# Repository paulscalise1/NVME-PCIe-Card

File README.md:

# NVME PCIe Card

A x4 PCIe to NVME adapter card for additional storage in PCIe Gen 4 and below compatable machines.
This board was created for the final project in ECEN 882 Passive Microwave Components at the University of Nebraska-Lincoln.

## PCB Design

## Validation

This board was tested with and on PCIe Gen 3 capable hardware. Read and write speeds top out near the real world limits of the hardware, thus proving at least PCIe Gen 3 performance metrics.

## TODO
Need to add full BOM.

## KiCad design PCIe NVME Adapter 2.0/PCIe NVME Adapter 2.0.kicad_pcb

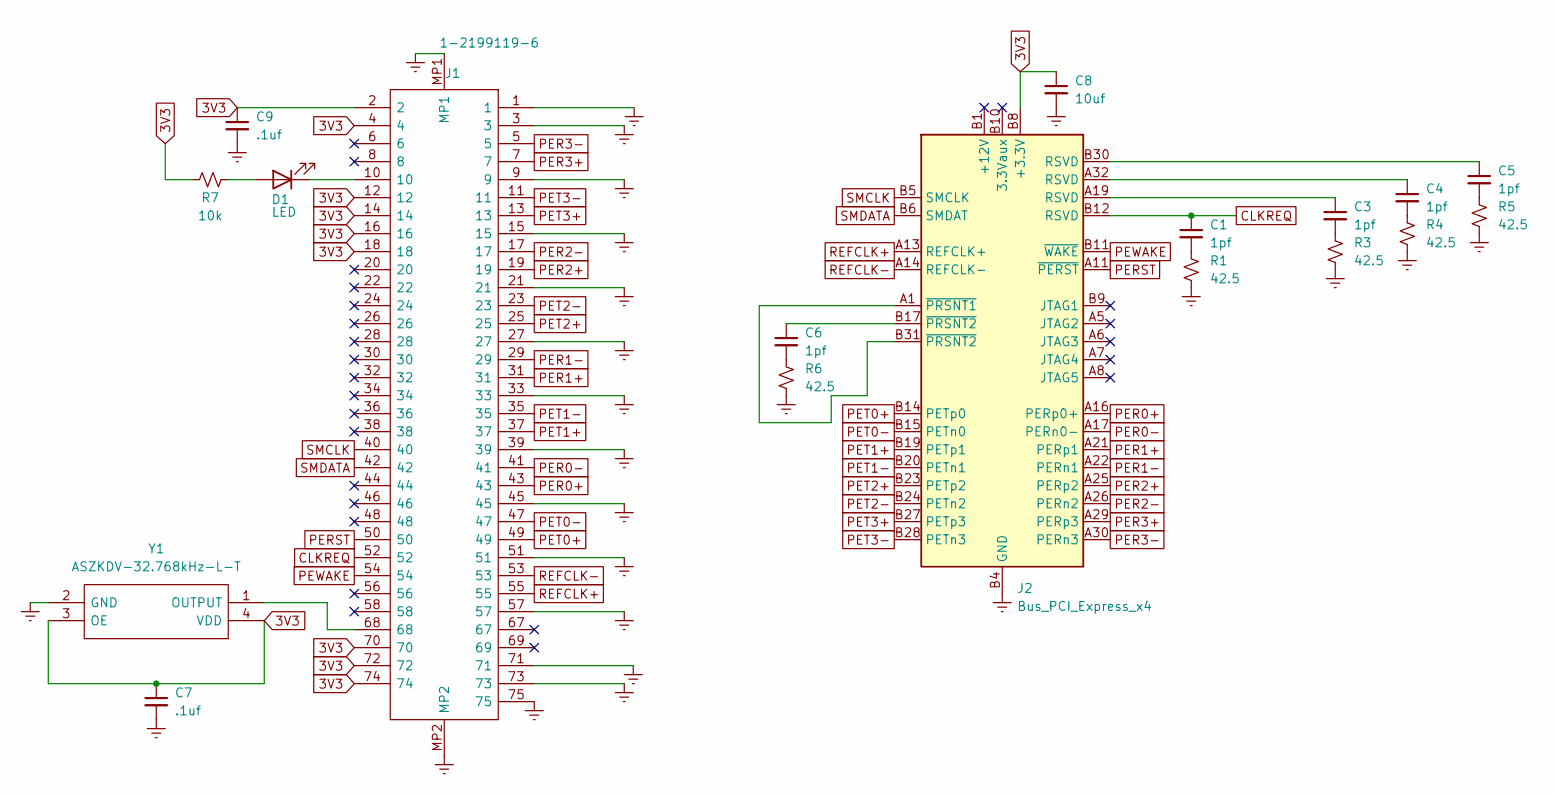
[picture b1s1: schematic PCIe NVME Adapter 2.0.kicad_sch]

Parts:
C1, C3, C4, C5, C6: 1pf; C_0402_1005Metric
C7, C9: .1uf; C_0402_1005Metric
C8: 10uf; C_0402_1005Metric
D1: LED; LED_0402_1005Metric
J1: 1-2199119-6; 121991196; Mouser Part Number 571-1-2199119-6
J2: Bus_PCI_Express_x4; BUS_PCIexpress_x4
R1, R3, R4, R5, R6: 42.5; R_0402_1005Metric
R7: 10k; R_0402_1005Metric
Y1: ASZKDV-32.768kHz-L-T; ASZKDV32768kHzLT; Mouser Part Number 815-ASZKDV32768KHZLT

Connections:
3V3: C7.1, C8.1, C9.1, J1.2, J1.4, J1.12, J1.14, J1.16, J1.18, J1.70, J1.72, J1.74, J2.A9 (+3.3V), J2.A10 (+3.3V), J2.B8 (+3.3V), R7.1, Y1.3 (OE), Y1.4 (VDD)
CLKREQ: C1.1, J1.52, J2.B12 (RSVD)
Earth: C7.2, C8.2, C9.2, J1.1, J1.3, J1.9, J1.15, J1.21, J1.27, J1.33, J1.39, J1.45, J1.51, J1.57, J1.71, J1.73, J1.75, J1.MP1, J1.MP2, J2.A4 (GND), J2.A12 (GND), J2.A15 (GND), J2.A18 (GND), J2.A20 (GND), J2.A23 (GND), J2.A24 (GND), J2.A27 (GND), J2.A28 (GND), J2.A31 (GND), J2.B4 (GND), J2.B7 (GND), J2.B13 (GND), J2.B16 (GND), J2.B18 (GND), J2.B21 (GND), J2.B22 (GND), J2.B25 (GND), J2.B26 (GND), J2.B29 (GND), J2.B32 (GND), R1.2, R3.2, R4.2, R5.2, R6.2, Y1.2 (GND)
unnamed: C1.2, R1.1
unnamed: C3.1, J2.A19 (RSVD)
unnamed: C3.2, R3.1
unnamed: C4.1, J2.A32 (RSVD)
unnamed: C4.2, R4.1
unnamed: C5.1, J2.B30 (RSVD)
unnamed: C5.2, R5.1
unnamed: C6.1, J2.B17 (~PRSNT2)
unnamed: C6.2, R6.1
unnamed: D1.2 (A), R7.2
unnamed: D1.1 (K), J1.10
unnamed: J2.A1 (~PRSNT1), J2.B31 (~PRSNT2)
unnamed: J1.68, Y1.1 (OUTPUT)
PER0+: J1.43, J2.A16 (PERp0+)
PER0-: J1.41, J2.A17 (PERn0-)
PER1+: J1.31, J2.A21 (PERp1)
PER1-: J1.29, J2.A22 (PERn1)
PER2+: J1.19, J2.A25 (PERp2)
PER2-: J1.17, J2.A26 (PERn2)
PER3+: J1.7, J2.A29 (PERp3)
PER3-: J1.5, J2.A30 (PERn3)
PERST: J1.50, J2.A11 (~PERST)
PET0+: J1.49, J2.B14 (PETp0)
PET0-: J1.47, J2.B15 (PETn0)
PET1+: J1.37, J2.B19 (PETp1)
PET1-: J1.35, J2.B20 (PETn1)
PET2+: J1.25, J2.B23 (PETp2)
PET2-: J1.23, J2.B24 (PETn2)
PET3+: J1.13, J2.B27 (PETp3)
PET3-: J1.11, J2.B28 (PETn3)
PEWAKE: J1.54, J2.B11 (~WAKE)
REFCLK+: J1.55, J2.A13 (REFCLK+)
REFCLK-: J1.53, J2.A14 (REFCLK-)
SMCLK: J1.40, J2.B5 (SMCLK)
SMDATA: J1.42, J2.B6 (SMDAT)

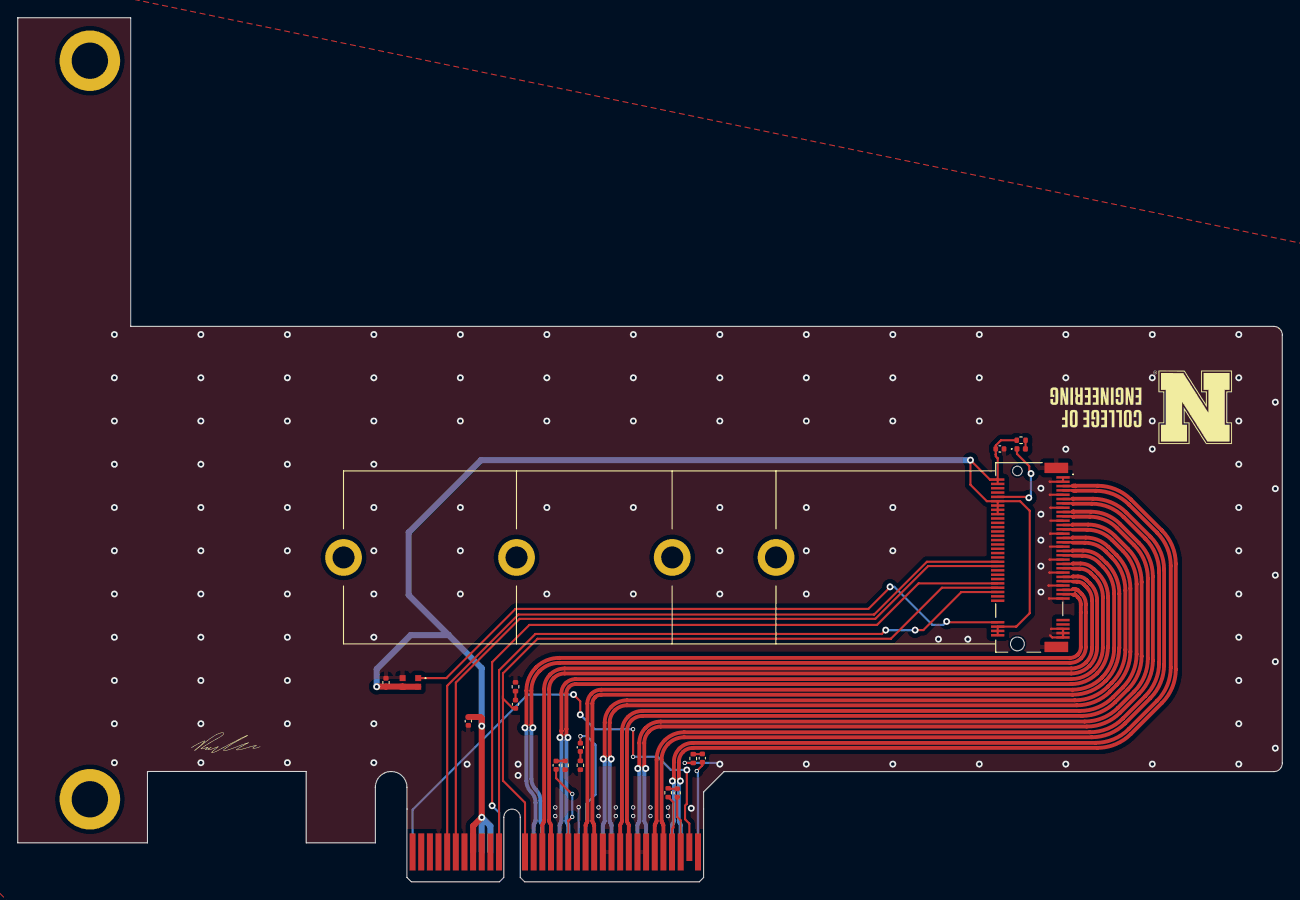
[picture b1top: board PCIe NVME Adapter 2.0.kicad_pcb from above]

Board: 2 copper layers, 146.2 x 99.9 mm, 18 parts (0 on the bottom side), 38 nets.

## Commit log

2025-07-03 init
2025-07-03 added photos
2025-07-03 fix photo
2025-07-03 readme
